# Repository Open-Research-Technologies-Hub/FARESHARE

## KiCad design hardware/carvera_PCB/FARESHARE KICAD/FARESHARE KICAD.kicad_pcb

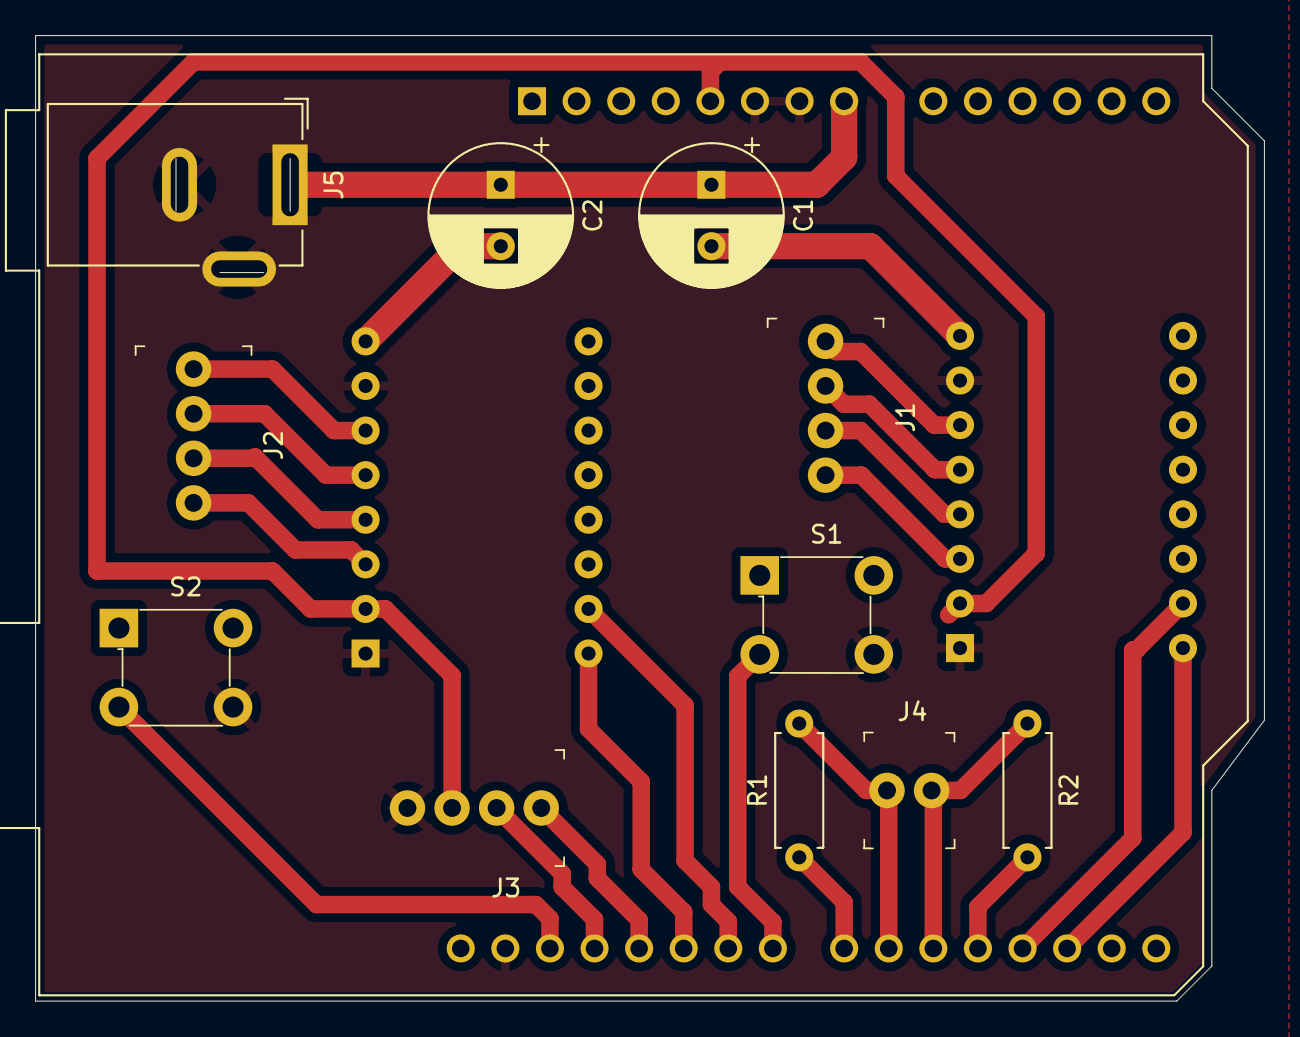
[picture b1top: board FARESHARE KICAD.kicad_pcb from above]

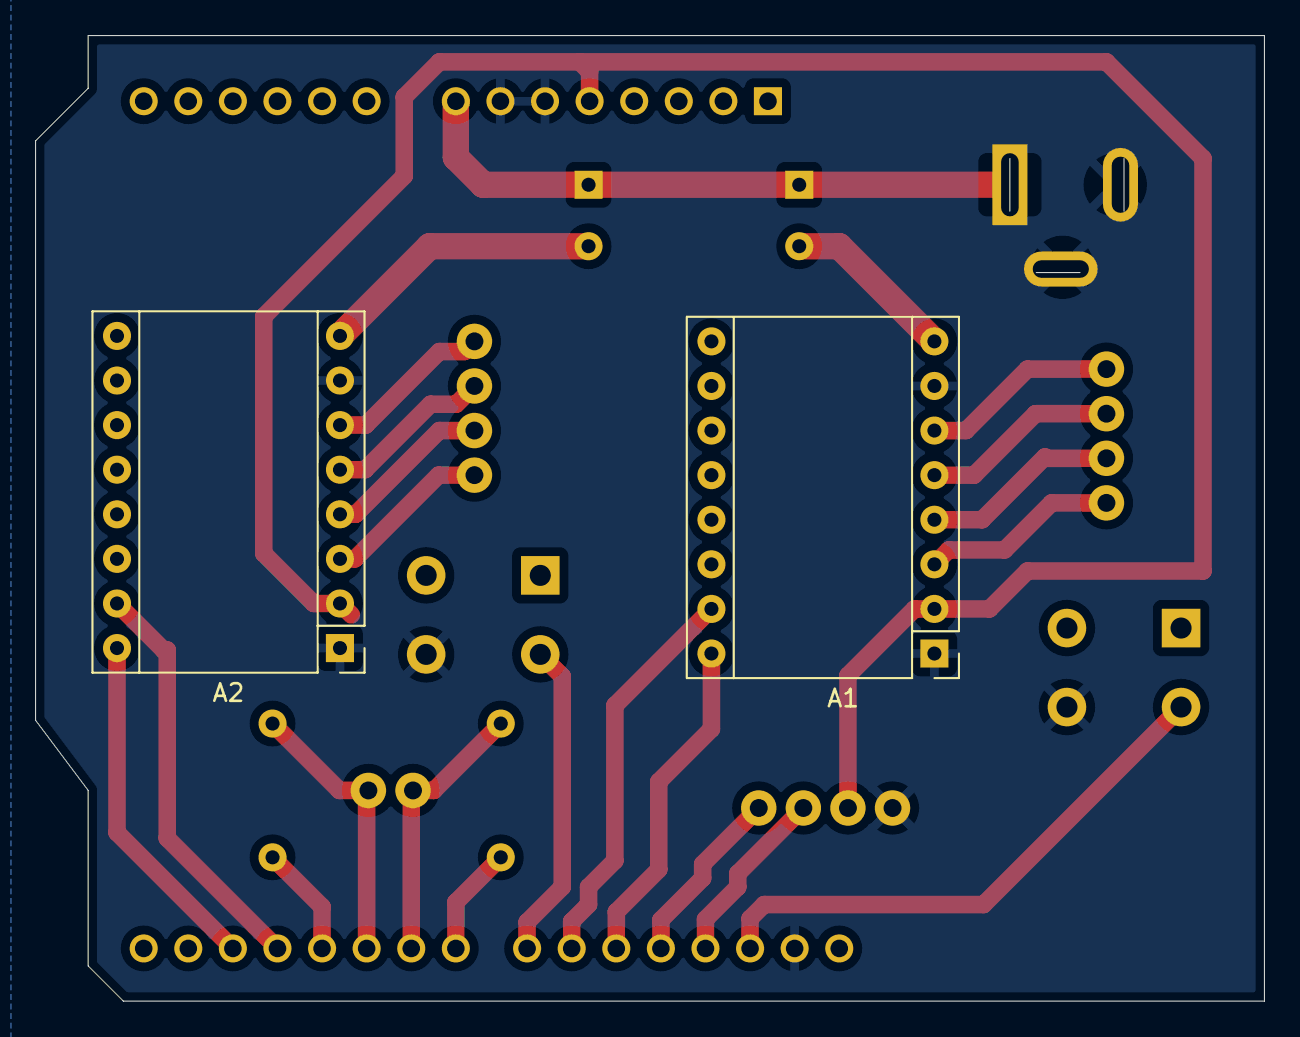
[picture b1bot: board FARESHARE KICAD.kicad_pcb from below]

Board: 2 copper layers, 70.0 x 55.0 mm, 14 parts (2 on the bottom side), 27 nets.

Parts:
A1, A2: Pololu_Breakout_A4988; Pololu_Breakout-16_15.2x20.3mm
A3: Arduino_UNO_R2
C1, C2: C_Polarized; CP_Radial_D8.0mm_P3.50mm
J1, J2, J3: 0022232041; PinHeader_1x4_P2.54mm_Drill1.02mm
J4: 22-23-2021; PinHeader_1x2_P2.54mm_Drill1.02mm
J5: Barrel_Jack_Switch_Pin3Ring; BarrelJack_GCT_DCJ200-10-A_Horizontal
R1, R2: R; R_Axial_DIN0207_L6.3mm_D2.5mm_P7.62mm_Horizontal
S1, S2: 1825910-6; Switch_Tactile_THT_6x6mm

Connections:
+5V: A1.2 (VDD), A2.2 (VDD), A3.5 (+5V), J3.3
+12V: A3.8 (VIN), C1.1, C2.1, J5.1
D2: A2.16 (DIR), A3.17 (D2)
D3: A2.15 (STEP), A3.18 (D3)
D4: A3.19 (D4), R2.2
D5: A3.20 (D5), J4.2, R2.1
D6: A3.21 (D6), J4.1, R1.2
D7: A3.22 (D7), R1.1
D8: A3.23 (D8), S1.3
D9: A1.15 (STEP), A3.24 (D9)
D10: A1.16 (DIR), A3.25 (D10)
D11: A3.26 (D11), J3.1
D12: A3.27 (D12), J3.2
D13: A3.28 (D13), S2.3
GND: A1.1 (GND), A1.7 (GND), A2.1 (GND), A2.7 (GND), A3.6 (GND), A3.7 (GND), A3.29 (GND), J3.4, J5.2, J5.3, S1.4, S2.4
unnamed: A1.4 (1A), J2.3
unnamed: A1.3 (1B), J2.4
unnamed: A1.5 (2A), J2.2
unnamed: A1.6 (2B), J2.1
unnamed: A1.8 (VMOT), C2.2
unnamed: A1.13 (~RESET), A1.14 (~SLEEP)
unnamed: A2.4 (1A), J1.3
unnamed: A2.3 (1B), J1.4
unnamed: A2.5 (2A), J1.2
unnamed: A2.6 (2B), J1.1
unnamed: A2.8 (VMOT), C1.2
unnamed: A2.13 (~RESET), A2.14 (~SLEEP)

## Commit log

2024-04-05 move things around and create an editable BOM
2024-04-19 move things around and create a board for carvera
2024-05-05 added kicad pcb file
2024-05-06 circuit components added
2024-05-07 Kicad files updated
2024-05-07 PCb design and gerber files generated
2024-05-07 Error corrected on Pcb and gerber file
2024-05-07 Pcb and gerber updated
2024-05-08 added silk screen
2024-05-08 added the schematic file
2024-05-08 gerbber files updated with a single sided pcb
2024-05-08 updated pcb+ gerber
2024-05-08 Cap size update
2024-05-09 changed power footprint
2024-05-10 changes on the barrel jack
2024-05-10 barrel jack updated to a round one
2024-05-10 Traces changed and other files updated accordingly
2024-05-10 trying to use edge cut to cut slots
2024-05-10 Will vias work?

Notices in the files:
hardware/carvera_PCB/FARESHARE KICAD/FARESHARE KICAD.kicad_pcb:
creativecommons.org/licenses/by/4.0
License: CC BY 4.0
